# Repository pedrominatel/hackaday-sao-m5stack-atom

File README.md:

# Hackaday SAO M5Stack Atom

This is the initial design for a SAO board for the [2025 Hackaday Conference Europe](https://hackaday.com/2025/01/14/hackaday-europe-2025-tickets-on-sale-and-cfp-extended-until-friday/) in Berlin.

This board was designed on KiCad v9.

## Overview

This SAO compatible board is based on the Apple Macintosh II for the [M5Stack AtomS3](https://docs.m5stack.com/en/core/AtomS3) (also compatible with any Atom).

### First Version for the Hackaday Conference Europe

### Front

### Back

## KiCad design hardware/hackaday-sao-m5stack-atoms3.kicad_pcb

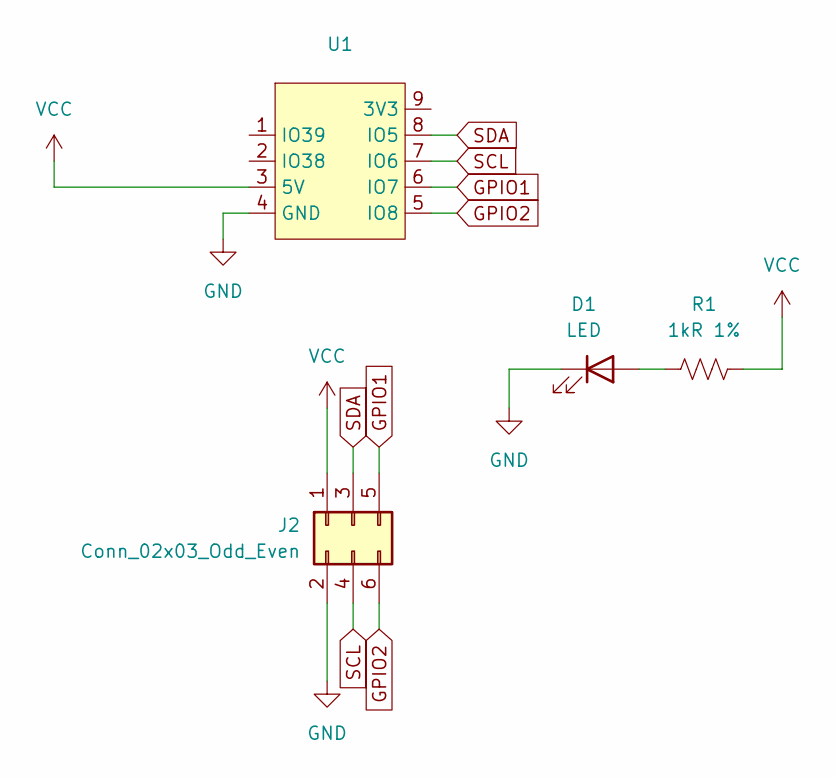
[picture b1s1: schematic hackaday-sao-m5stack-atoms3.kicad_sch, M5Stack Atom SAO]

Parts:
D1: LED; LED_0603_1608Metric
J2: Conn_02x03_Odd_Even; IDC-Header_2x03_P2.54mm_Vertical
R1: 1kR 1%; R_0603_1608Metric
U1: AtomS3

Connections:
GND: D1.1 (K), J2.2, U1.4 (GND)
GPIO1: J2.5, U1.6 (IO7)
GPIO2: J2.6, U1.5 (IO8)
unnamed: D1.2 (A), R1.1
SCL: J2.4, U1.7 (IO6)
SDA: J2.3, U1.8 (IO5)
VCC: J2.1, R1.2, U1.3 (5V)

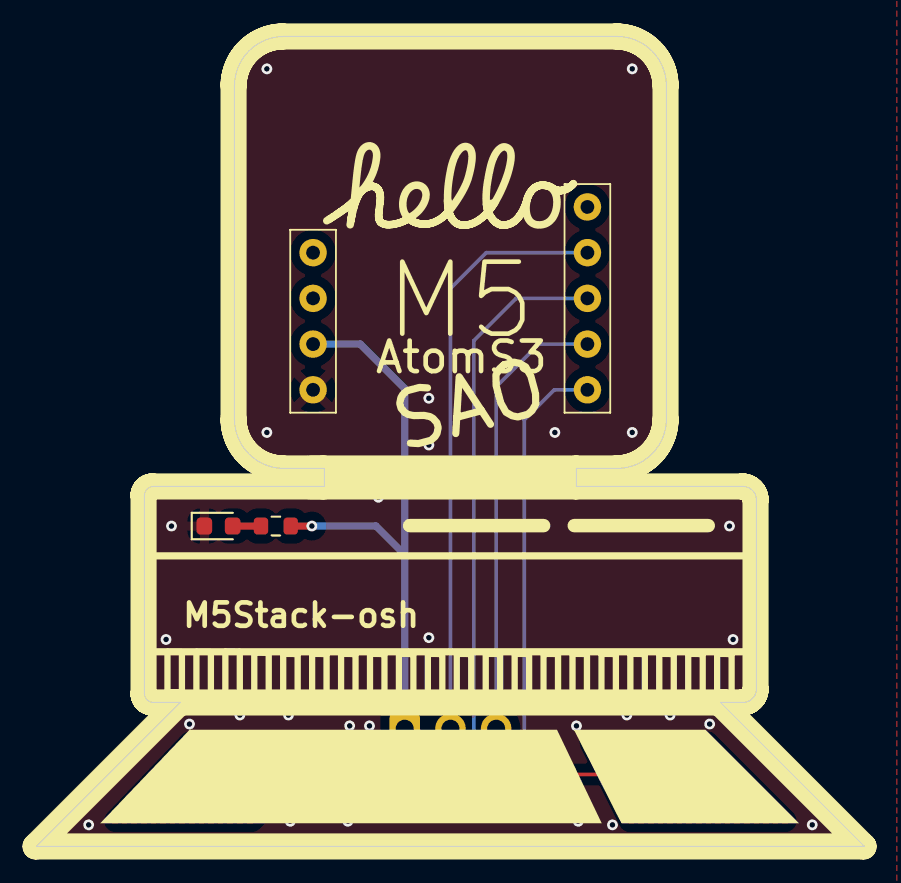
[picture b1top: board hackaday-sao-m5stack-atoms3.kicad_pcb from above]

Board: 2 copper layers, 46.0 x 45.0 mm, 4 parts (1 on the bottom side), 7 nets.

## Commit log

2025-02-13 Added the v0.1 board project
2025-02-14 Added version 0.1
2025-02-14 Readme updated
2025-02-14 Add sao board v0.1 (#2)
    * Added version 0.1
    * Readme updated
2025-03-15 Readme updated and new version added
2025-03-15 Project updated
2025-03-15 Typo fixed
2025-03-15 Board update (#3)
    * Project updated
    * Readme updated and new version added
    * Typo fixed
